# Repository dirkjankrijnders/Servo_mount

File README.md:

Servo mount
===========

Based on several threads on the dutch three-rail model railroad forum (for example [here](http://forum.3rail.nl/index.php?topic=36707.msg814683#msg814683)), I came up with the idea to combine a PCB of say a decoder with the mechanical mounting of a servo. (cheap to manufacture on small scale and very precise). The result:

Revision 1
----------

The design is based on the [PSSD](https://github.com/dirkjankrijnders/PSSD), however using a different microcontroller (attiny84) for more memory options and smaller footprint. The construction also meant sacrificing the buttons, so another way of programming the decoder was needed. The ISP connector already planned also has the I2C lines available, so the decoder can now be configured by setting registers over I2C. An arduino sketch facilitates this process.

The decoder has not yet been tested on the PCB, but works on the breadboard. It support two servo's, so only half of the PCB's need their components placed, the second servo can be connected via standard servo wires.

Revision 2
----------
I already found some issues with the electronics side of the decoder, so a second revision is planned. The second revision fixes most footprint issues as well as allowing mount in both left and right switches. Also all components have been moved to the back of the PCB so the build decoder should flush in the C rail ballast form. A good count of the I/O ports shows that there are three unused, these could be used for manual switch buttons.

What is missing? Exactly, the hole for the servo. But a drill can fix that, the 3rd revision will have a hole with the proper shape. Drilling the hole however severed some traces, so those have to be botched, also fixed in the third revision.

After those mechanical problems the electronics all work! So the work on the firmware commenced in full, as per August 16th speed control and a programmer for the I2C interface have been implemented. The manual switch button remain to be implemented.

Revision 3
----------
PCB's for rev.3 were ordered on December 2nd and the changes are:
- Footprint for G-90 servo's
- More I/O pads
- Shape changes to fit under 2471? switches
- moved the solder pads of C4 and the rail power as to not make short-cut contact when the lever passes.

Pictures follow when the boards arrive
Cost/BOM
--------

<table>
<tr>
<th>Part</th><th>#</th><th>Reichelt #</th><th>price* (€)</th>
</tr>
<tr><td>IC1</td><td>1</td><td>ATTINY 44A-SSU</td><td>1.07</td></tr>
<tr><td>D1</td><td>1</td><td>SMD DF 005</td><td>0.18</td></tr>
<tr><td>U1</td><td>1</td><td>µA 78L05 SMD</td><td>0.15</td></tr>
<tr><td>U2</td><td>1</td><td>BUZ 11</td><td>0.57</td></tr>
<tr><td>R*,C*</td><td>2</td><td></td><td>0.50**</td></tr>
<tr><td>PCB</td><td>1</td><td>Seeed</td><td>1.00</td></tr>
<tr><td colspan=3>Total</td><td>3.47</td></tr>
</table>
\* Estimate for orders of 10.<br/>
\** SMD 0805 Components from cost almost nothing in bulk (&gt; 10)

Firmware
--------
To make to PSSD firmware:

	make BOARD=CSMD

To set the fuse and program both flash and eeprom:

	avrdude -p t44 -U lfuse:w:0xe2:m -U hfuse:w:0xdf:m -U efuse:w:0xff:m
	make flash BOARD=CSMD

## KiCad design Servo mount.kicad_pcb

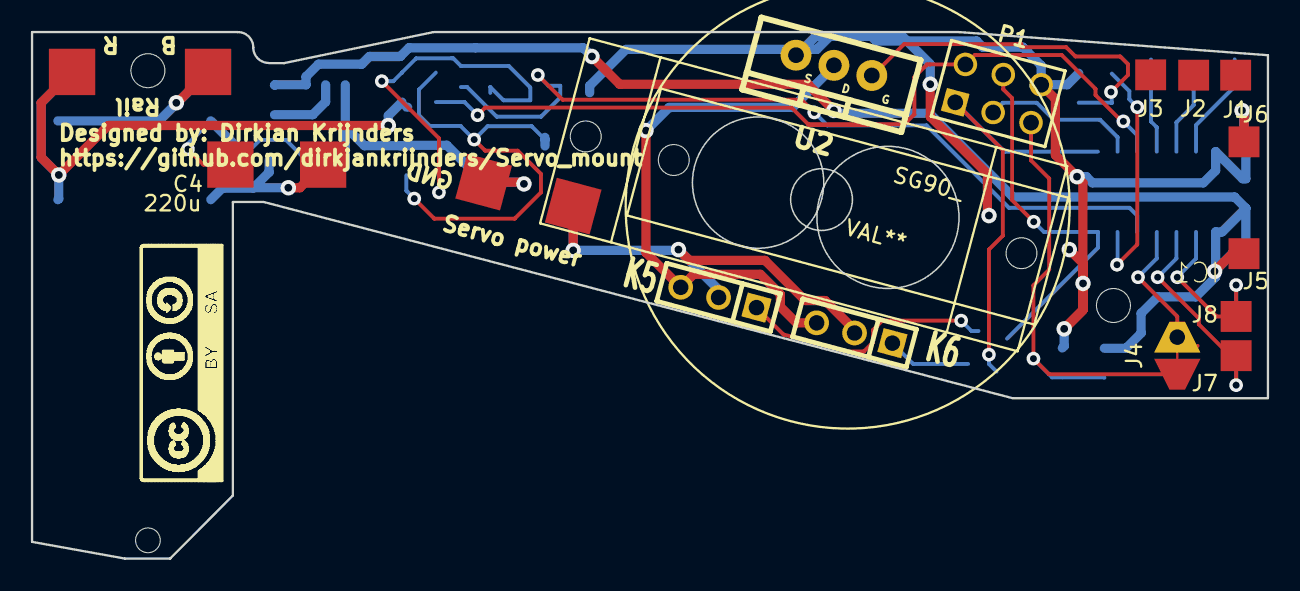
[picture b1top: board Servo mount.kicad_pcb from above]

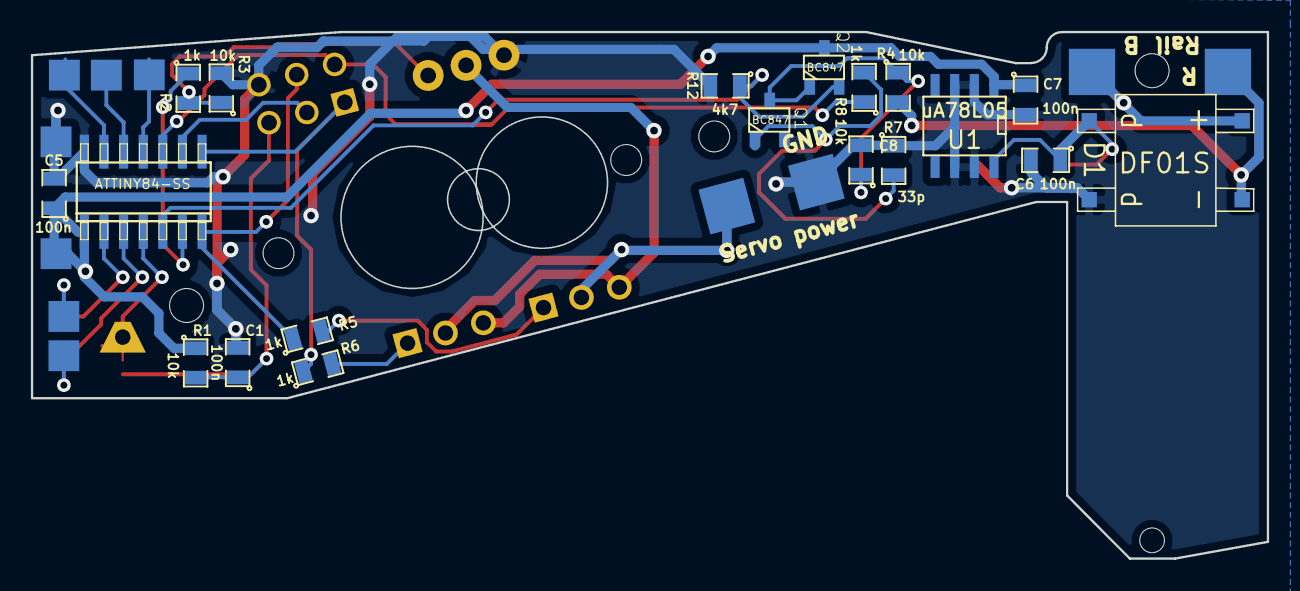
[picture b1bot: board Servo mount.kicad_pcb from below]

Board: 2 copper layers, 80.0 x 34.1 mm, 33 parts (19 on the bottom side), 24 nets.

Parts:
C1, C5, C6, C7: 100n; SM0805
C4: 220u; Solderpad_2
C8: 33p; SM0805
D1: DF01S; DIPSMD4
IC1: ATTINY84-SS; SOIC-14
J1, J2, J3, J5, J6, J7, J8: SOLDER_PAD; solder_pad_2mm_fb
J4: solder_jumper_conn
K5, K6: CONN_3; SIL-3
P1: CONN_3X2; pin_array_3x2
Q1, Q2: BC847; SOT23
R1, R3, R4, R7: 10k; SM0805
R2, R5, R6, R8: 1k; SM0805
R12: 4k7; SM0805
SG90_: VAL**; Combined_servo
U1: uA78L05; SO8E
U2: BUZ11; TO-220_FET-GDS_Vertical

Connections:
+5V: C5.1, C7.1, IC1.1, J5.1, Q2.3, R1.1, U1.1
AGND: K5.3, K6.3, U2.2
DIS_SIGNAL: IC1.10, P1.2, R8.1
GND: C1.2, C4.2, C5.2, C6.2, C7.2, C8.2, D1.1, IC1.14, J6.1, P1.6, Q1.2, R3.2, R7.1, R12.2, U1.2, U1.3, U1.6, U1.7, U2.3
GND FET: IC1.6, R2.1
MISO: IC1.8, P1.1, R6.1
MOSI: IC1.7, P1.4, R5.1
unnamed: C4.1, C6.1, D1.3, U1.8
unnamed: C8.1, Q1.3, Q2.1, R4.1
unnamed: IC1.2, J8.1
unnamed: IC1.3, J7.1
unnamed: IC1.4, J4.2
unnamed: IC1.11, J3.1
unnamed: IC1.12, J2.1
unnamed: IC1.13, J1.1
unnamed: K5.1, R5.2
unnamed: K6.1, R6.2
unnamed: Q1.1, R7.2, R8.2
unnamed: R2.2, R3.1, U2.1
Rail signal: IC1.5, Q2.2, R12.1
Reset: C1.1, J4.1, P1.5, R1.2
SCK: IC1.9, P1.3
VAA: D1.4, R4.2
VCC: K5.2, K6.2

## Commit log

2013-11-07 Restored AVR ISP Programming, started PCB layout
2013-11-18 Layed out board
2014-02-18 Rev. 0 as send to OSHPark
2014-02-18 More ignores
2014-02-18 Image of prototype
2014-02-25 Changed SOIC-14w to SOIC-14
    Close #3
2014-03-06 Fixed rectifier pinout, added front ground plane, closes #2
2014-03-06 Updated read me with BOM, closes #5
2014-03-11 Solderpads for I/O (closes #1), reset solder jumper
    Added solder pads for remaining I/O pins on the microcontroller, closes
    #1
    Change the reset jumper to a normally connected solder jumper with
    through hole for debug wire.
2014-03-13 Updated schematic to fix wrong servo pins
2014-03-13 Fixed servo connection pins (closes #8) and servo connector holes (closes #6)
2014-03-13 Fixed DRC errors
2014-03-20 Final board shape, new kicad version
2014-05-19 Added artwork sources
2014-05-19 Added firmware section
2014-05-21 Fixed image link
2014-05-21 Fixed rev 1 issues
    - Moved all pad away from foot to allow for mounting under crossing
    - Fixed the “hole” for the servo
    - Fixed the order of J4 to really allow debug wire access
2014-08-16 Updated for newest firmware and rev two troubles
2014-08-16 Moved tracks away from servo hole
2014-08-18 Added ignore of autosave files
2014-08-18 Fixed GND connection servo, fixed TO220 footprint
2014-08-20 Clean schematic library
2014-08-20 - Updated schematic to the new standard libraries
2014-09-04 Adapted Board shape to 247?? points
2014-10-25 Adepted PCB shape for 24712
2014-10-29 Updated shape for 24712, made more GND connections
2014-11-03 Brought out more I/O, option for larger servo
2014-11-03 fix footprints Q1 and Q2
2014-11-22 Panel with two PCB's and the combined footprint for SG-90 and micro- Servo's
2014-12-03 Updates to rev. 3x
2014-12-03 Added info on revision 3
2014-12-10 Update gitignore
2015-04-08 Added production files for rev.3
2015-11-23 Reconnected wires after library upgrade
2015-11-23 Reconnected wire after library upgrade
